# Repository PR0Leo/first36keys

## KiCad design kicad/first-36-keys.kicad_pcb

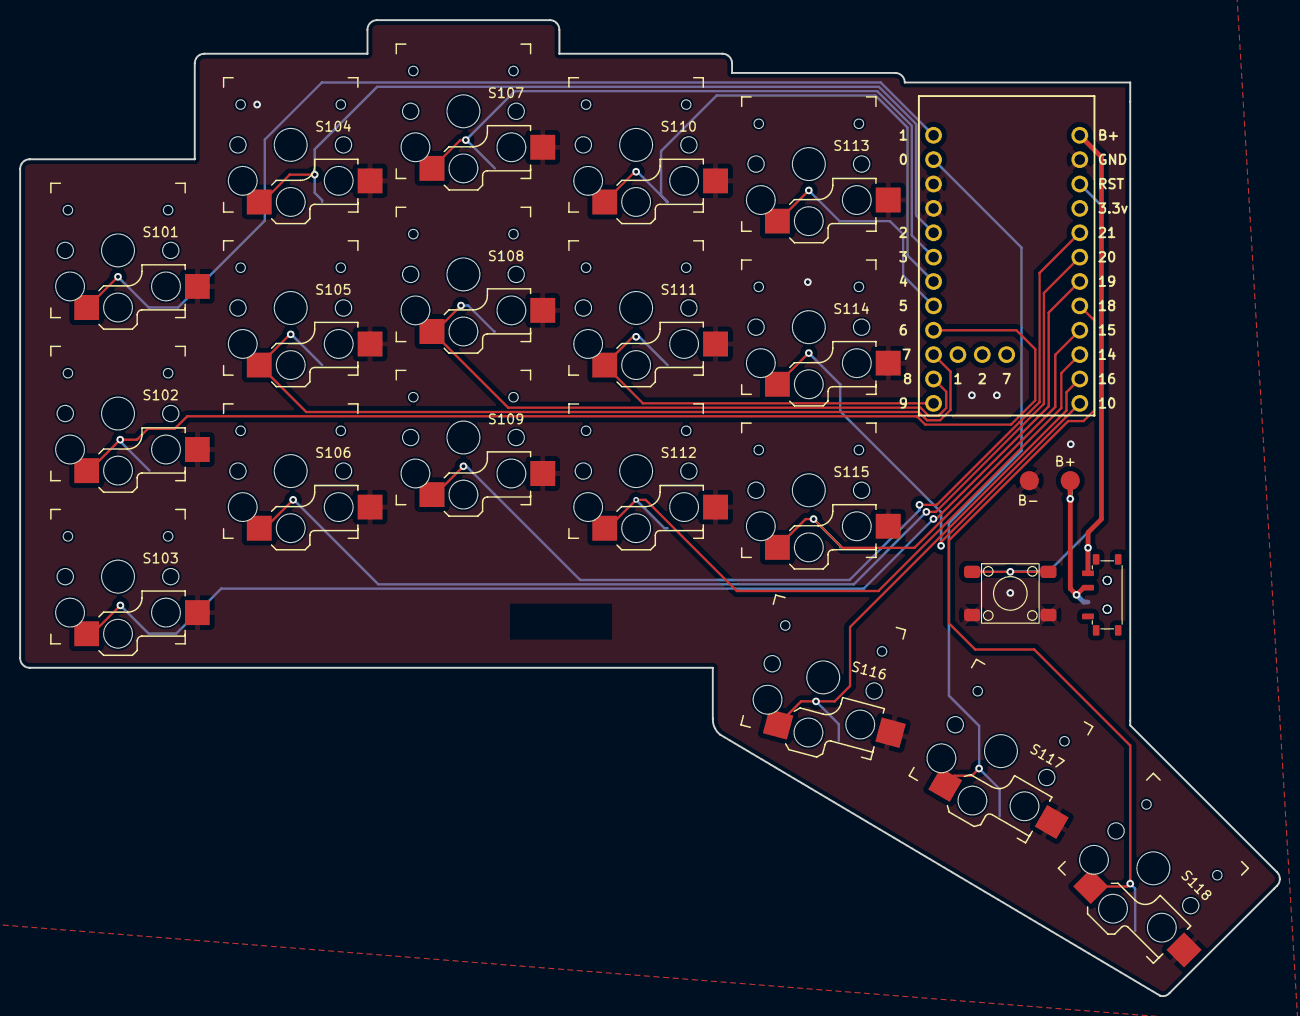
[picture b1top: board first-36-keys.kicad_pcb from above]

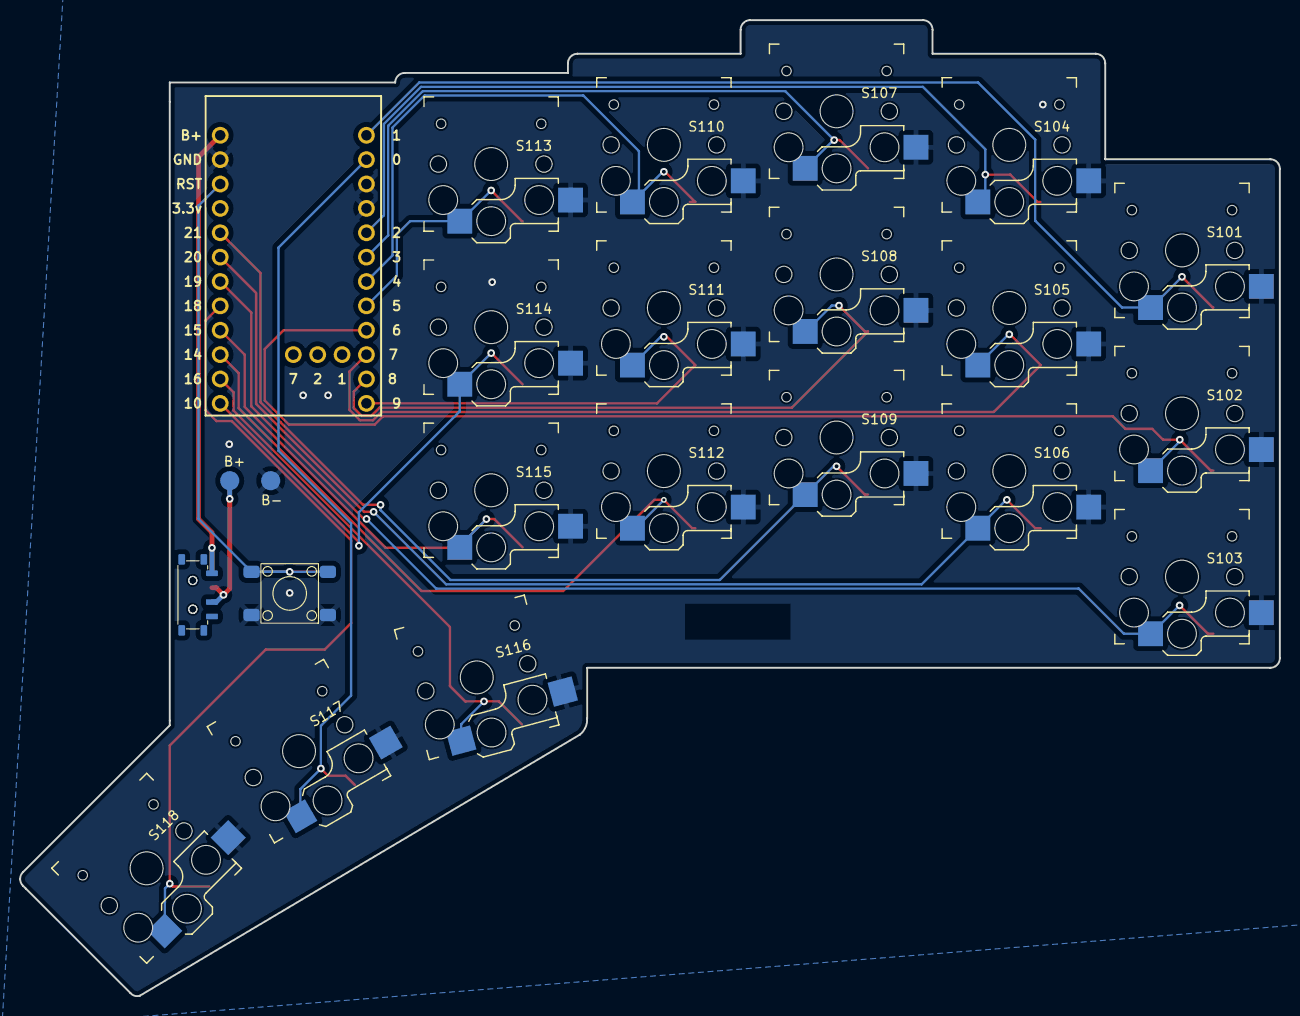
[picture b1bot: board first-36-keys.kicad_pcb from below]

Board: 2 copper layers, 131.3 x 101.7 mm, 27 parts (4 on the bottom side), 22 nets.

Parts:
B+: 2.0mm; TestPad_2.0mm
B+#2: 2.0mm; TestPad_2.0mm
B-: 2.0mm; TestPad_2.0mm
B-#2: 2.0mm; TestPad_2.0mm
PS101: SW_MSK12C02-HB
R102: WE_430182050816
S101, S102, S103, S104, S105, S106, S107, S108, S109, S110, S111, S112, S113, S114, S115, S116, S117, S118: Keyswitch; Kailh_socket_PG1350_reversible
U101: Nice_Nano_V2
ps102: SW_MSK12C02-HB
r101: WE_430182050816

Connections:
GND: B-.1, B-#2.1, R102.2, S101.2, S102.2, S103.2, S104.2, S105.2, S106.2, S107.2, S108.2, S109.2, S110.2, S111.2, S112.2, S113.2, S114.2, S115.2, S116.2, S117.2, S118.2, U101.3 (GND), U101.4 (GND), U101.23 (GND), r101.2
unnamed: B+.1, B+#2.1, PS101.2 (B), ps102.2 (B)
RST: R102.1, U101.22 (RST), r101.1
S1: S101.1, U101.1
S2: S104.1, U101.5 (2)
S3: S107.1, U101.6 (3)
S4: S110.1, U101.7 (4)
S5: S113.1, U101.8 (5)
S6: S102.1, U101.9 (6)
S7: S105.1, U101.10 (7)
S8: S108.1, U101.11 (8)
S9: S111.1, U101.12 (9)
S10: S114.1, U101.13 (10)
S11: S103.1, U101.18 (19)
S12: S106.1, U101.19 (20)
S13: S109.1, U101.20 (21)
S14: S112.1, U101.15 (14)
S15: S115.1, U101.16 (15)
S16: S116.1, U101.14 (16)
S17: S117.1, U101.2 (0)
S18: S118.1, U101.17 (18)
b+: PS101.3 (C), U101.24 (B+), ps102.1 (A)

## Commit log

2025-12-05 addedSoftware
2025-12-05 updatedEverything
2026-02-11 test
2026-02-11 changedyml
2026-02-11 changedymlwith
2026-02-11 changedfilepath
2026-02-11 configpath
2026-02-11 test2
2026-02-11 test3
